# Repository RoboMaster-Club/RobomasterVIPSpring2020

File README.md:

# RobomasterVIPSpring2020

This is the repository for the VIP associated with the Purdue Robomaster team to create a self-guided missile system for the International Robomaster Competition in the Spring 2020 semester. The progress for the project will be documented here and the documentation for each subsystem can be found in their respective folder.

## Overview

The Robomaster 2020 competition added a new robot named the "dart". The dart is a self-guided missile system that will travel across the game field and deal damage to the enemy team's base. The team is also responsible for the creation of a dart launcher that will launch the darts. A more in-depth overview can be found [here](https://docs.google.com/presentation/d/1Q_qpdWloxJJ2q0ATfSRlsLZs0-6WAkRAROG2gjLVUHA/edit?usp=sharing). The dart build specification can be found in the [Robomaster Robot Specification Manual](http://rm-static.djicdn.com/documents/13194/b4177a18f71e31577802511685160062.pdf).

## Team Members

* Kurtis Dressel
* Henry Silva
* Dansen Wang

## Updates

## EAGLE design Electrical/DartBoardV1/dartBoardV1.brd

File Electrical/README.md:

# Dart Electrical Subsystem

## Contributers
* Henry Silva

## Updates

### Week 12 (4/6 - 4/11)

The team has decided to switch to SPI instead of using i2c because of its speed advantages and because there are only 2 slave devices on the dart. I will now go on a long winded account of how I got spi to work on the stm32 with an arduino as slave because if I dont write this down I am going to forget. I tested both full duplex slave and half duplex recieve only with both hardware nss diasbled and enabled all of them worked. I did not figure out how to do an interrupt with the hardware nss but I was able to simulate slave select by creating a gpio input on PC2 that acted as a slave select. The stm32 will only try and listen when PC2 is held low. To recieve the data sent by the arduino use HAL_SPI_Receive. I had issues with the stm32 reading the sent data incorrectly. I was able to fix this with 2 changes. 
1. Inserting a small delay (10 milliseconds) between the arduino pulling the slave select low and sending the data. 
2. Setting the number of bytes to recieve in the HAL_SPI_Receive call by 1 more than the number of bytes that you wish to recieve
3. A relatively small timeout period (50 milliseconds) on the HAL_SPI_Receive call.

This ensures that the stm32 will read the data being sent to it completely and correctly. This will cause the SPI recieve function to timout every time it is called, but with a short timeout period this should not effect the speed too much. The timeout period may have to be increased if the amount of bytes being read is increased by a lot.

### Week 11 (3/29 - 4/5)

Since we have decided to use the stm32 and the raspberry pi, a way to communicate between the two is needed. I2C seems like a good choice because it would allow the raspberry pi to use one protocol to communicate with the accelorometer and the stm32. In the I2C system, the master would be the raspberry pi and the stm32 and any other sensor would be the slave devices. The raspberry pi would first initialize any sensors on board and send any initial data to the stm32. The commands to the stm32 would be sent by the pi and stored in some of the data registers on the stm32.

### Week 9 (3/15 - 3/22)

Given the new situation that we are in, I have decided to prioritize what I think can be realistically done while not on campus and better prepare for a testing prototype to be completed early next fall semester. Currently, I am tasked with creating the magnetic actuators and making a testing interface for the test rig. I am not confident that I can produce the coils needed for the magnetic actuator at home, at least of the quality that would be acceptable for a testing prototype. I already have actuators that I could test the electronics with and could create more if needed, but not for flight test purposes. I could make progress on the research and development of the methods to create the magnetic actuators. The current plan is to either 3D print the coil wrapping base and wrap it with tape or 3d print a mold to make it out of wax.

For the testing interface, the dart would not need to run off of the onboard raspberry pi. An outside control system can be used instead. This gives me the freedom to choose any platform to run the test rig. The requirments of the testing interface would be live, fine control of the control surfaces of the dart and to recieve data from the sensors on the dart such as the accelerometer and gyro. Data from the change in angle of the dart and what the actuators are set to will be neccessart to create the autonomous control system for the dart. I first considered using an arduino, but having a digital interface with keyboard and controller inputs would be difficult to create from scratch. This is also the same problem for using a raspberry pi. Based on my advisors suggestion, I looked into using a myRio. This solution seems attractive because labview can be used to easily create a testing interface that can also display live data. The only problem with this solution is that I do not have a myRio and they are not cheap. I would have easily been able to borrow one from the ME department, but I am no longer on campus.

### Week 7 (3/1 - 3/7)

Following the decision to use the raspberry pi zero for the vision processing, I was tasked with finding a way to control the magnetic actuators and get data from the imu either with the raspberry pi or by interfacing the pi with a microcontroller. After discussing with others with more experience, I decided to use an stm32 along with the pi.Since the pi will be doing vision processing it will be more reliable to send commands for the stm32 to perform rather than having the pi create pwm signals and communicate with the imu. This also means that the stm32 will have to communicate information back to the pi. I was then faced with two decisions, either send IMU data to the pi and have the pi calculate the appropriate actions for the stm32 to perform or have the pi send vision data to the stm32 and have the stm32 determine the appropriate actions for the actuators. I decided on the first option because it keeps the control calculations on the pi, which already has the vision data, and it would be faster to develop code for the pi. 

My first step to implementing the new changes was to update the elecitrcal schematic. I noticed that the current micrcontroller was the stm32f407. The 407 was chosen because of its camera interfacing features, but those are no longer needed in the new design. I decided to switch to the stm32f05, the same microcontroller on the [adafruit feather express](https://www.adafruit.com/product/4382). This will allow to test on a platform that I already have. It is also smaller than the stm32f07 and does not come with features that are not needed. After updating the schematic with the new microcontroller and motor drivers. I also had to connect the pi to the stm32f405 so that they can communicate with each other. I connected the TX and RX pins on the Pi to the RX and TX pins on the stm32f405. I used stm32CubeIDE to assign the pins on the stm32f405 to their functions. From previous experience, when communicating through uart between two devices you have to make sure that they are using the same uart protocol. The two most common are ttl and rs232. After some research, I found out that the pi uses ttl which the stm32 also uses, so no converter would be needed.

The next step was to find connectors to connect the battery and magnetic actuators. Given the size constraints, micro jst connectors with 1mm pitch would be the smallest solution to the problem. The [header](https://www.digikey.com/product-detail/en/jst-sales-america-inc/SM02B-SRSS-TB-LF-SN/455-1802-1-ND/926873), [housing](https://www.digikey.com/product-detail/en/jst-sales-america-inc/SHR-02V-S-B/455-1377-ND/759866), and [contact](https://www.digikey.com/product-detail/en/jst-sales-america-inc/SSH-003T-P0-2-H/455-2963-1-ND/5725854) are all really small and will probably be difficult to crimp, but it is worth it because of the small size of the board. One concern is that the current limit is 1 Amp, so if the whole circuit or any of the actuators needs to draw over an amp another solution will have to be found.

### Week 6 (2/23 - 3/1)

At the start of this week, I ordered the parts for the next magnetic actuator prototype. I bought the [DRV8835 Dual Motor Driver Carrier](https://www.pololu.com/product/2135) from Pololu. For the magnets, I ordered two different sizes, one for the [inner magnet](https://supermagnetman.com/products/cyl0052?_pos=1&_sid=c6e9fa681&_ss=r&variant=11410243843) and [another](https://supermagnetman.com/products/d1001b?_pos=1&_sid=058eb5170&_ss=r&variant=11410255619) for the outside centering magnet. For the inside of the actuator two of the magnets will be placed in between the pivoting rod. Two of the outer magnets will be used to center the inner magnets when the actuator is not powered. They will also be used to provide a counter torque to enable the degree of rotation based on the PWM signal.

After getting the new magnets, a new prototype for the actuator was designed and printed. The new design is smaller and is closer to the size that we will want it to be to go on the dart. After the magnets were placed in the rotating part of the actuator and the wire coiled around the outside, the tests were ready to begin. The code I used to test the actuator can be found [here](https://github.com/RoboMaster-Club/spring-2020-vip-course/blob/master/Electrical/driverTest/driverTest.ino). I conducted test on both the old and new prototype. I first tested moving the actuator from one side to the other. Both the new and old prototype were able to do this quickly and with reasonable force. The second test used magnets on the outside along with changing the pwm signal to control the angle of the actuator. I was able to control the angle, but the movement between angles was not perfectly smooth and the actuator would sometimes get stuck. This is most likely due to the magnets on the outside not being perfectly straight or held in place. There is also no bearing on the inside of the actuator and the coil is not perfectly wrapped. Smoother movement was able to be done by increasing the voltage put through the coil, but it was still not perfect. The new prototype drew 0.8 amps at 2 volts and just over 1 amp at 2.5 volts. It also would get hot when run for longer than 30 seconds at 2.5 volts, but could run for a prolonged period of time without getting hot at 2 volts. These findings raise some concerns for my plans to run the actuators at the battery voltage (3.7 volts). The heat is not an issue because of the short flight time, but the current motor driver has a current limit of 1.2 amps per output channel. More tests will have to be done with the final design of the actuator to determine if a buck converter will be needed to drive the actuator.

Old design side to side

Old design angle control

New design angle control

### Week 5 (2/17 - 2/23)

Since the pcb would need a motor driver in order to provide enough current to use the magnetic actuator, I started my search for an appropriate motor controller. The first one I found was the [L298](https://www.sparkfun.com/datasheets/Robotics/L298_H_Bridge.pdf) full bridge motor driver. It looked like a good choice for a motor controller because it had 4 outputs for the 4 actuators that would be on the dart. It also has a max current output of up to 4A, which is more than enough to run the actuators. I replaced the 4 servo outputs with the new motor driver on the current dart schematic. I then realized that I would need a buck converter to step down the voltage from 3.7V to 3.3V that would run the logic, ATMEGA, and IMU. I used the [LM3671](http://www.ti.com/product/LM3671) that I have used in past projects. I would also need to boost the 3.7V to 5V to power the motor driver and actuators, but after some research into a converter I decided to look for 3.3V motor drivers because it would be inefficient to convert to 5V just for the motor driver and it would make the circuit smaller is everything ran on 3.3V. I found [this website](https://www.pololu.com/category/11/brushed-dc-motor-drivers) with many motor driver breakout boards for smaller motors. The actuators would not need the higher current output of the previous motor driver, so using a lower current one would not be a problem. The motor drivers on the site had only 2 outputs max, so I would need 2 of the drivers to control all the actuators. I decided on the [DRV8835](https://www.digikey.com/product-detail/en/texas-instruments/DRV8835DSSR/296-30391-1-ND/3188673) because it is small and can output a max current of 1.5A and runs off of 3.3V logic.

Using the guide that I found last week to make a magnetic actuator, I attempted to make one using some neodinium magnets and magnet wire I bought. I used a L298 breakout board as the motor driver. I first make a coil by wrapping around a pencil and turned the wire about 100 times. After hooking up the coil to the motor driver controlled by an arduino nano, I was not able to get a reaction from the magnet. I decided that I did not wrap the coil around enough and made another coil with about 500 turns. The coil was big compared to the magnet, but I was able to vibrate the magnet when I brought it close to the coil. I considered the test a minor success given that I was able to get a reaction out of the magnet.

After the team meeting on friday, another team member and I wanted to try to make a working prototype actuator based on the design from the guide. We 3D printed the actuator which was made up of a cylinder with another piece with pegs that held the magnet within it. The coil was wrapped around the cylinder using a drill to make a tight coil. We tested the actuator by hooking it directly up to a power supply with 1 volt output. At 1 volt, the actuator drew half an amp. The state of the actuator could be controlled by switching the polarity. The actuator was able to switch quickly and with reasonable force.

Goals For Next Week:
* Make another actuator prototype with new design, smaller magnets, and new motor driver
* Keep schematic updated and make changes as needed

### Week 4 (2/9 - 2/16)

I was tasked with getting the position of the dart from the launch point by using data from the accelerometer. After a bit of research, I decided that it would not be a good idea. I explain more about it at the end of my update report from last week. Since I abandoned that objective, I decided that making more progress on the custom pcb would be a good idea. My current schematic uses the stm32f4 as the microcontroller, but I am not confident in making that decision for the rest of the team. I decided to make another schematic using the atmega328p as the micro. I also decided to make a table of all the components on the dart and their power consumption. To find the voltages and draw, I looked at the datasheets for the atmega, pixy2, and the IMU. I was not able to find a data sheet for the servos, but after some research I concluded that the servos would draw about 200 mA between all of them since they would not be under high load. I did not know the power draw of the dart trigger device, but my guess is that it is minimal. Since the dart will only have to be on for less than 30 minutes and only flying for 5 seconds, a small battery will work just fine. A capacitor would require a constant power connection to the dart launcher and would also require an outside contact on the dart.

|Device|Voltage (V)|Power Draw (mA)|Watts|
|----------|------|----------|------|
|atmega328p|	3.3	|1.5|	0.00495|
|pixy2|	5	|140|	0.7|
|lsm6ds3|	3.3	|1	|0.0033|
|Servo (3)|	5|200|	1|
|DTD|	?	|?	|?|

After the team meeting on friday, I got a clearer message of what we want to use onthe dart. It was decided that the atmega328p would be the microcontroller on the dart. The body of the dart was also changed from a lifting body to a more missile shaped projectile. This would change the dimensions of the electronics board, but it will still have enough space to fit everything. Based on the suggestions of one of the faculty advisors, we are going to try and switch from servos to a magnetic actuator. A magnetic actuator is a magnet placed in a coil of wire. Driving current through the wire will cause a magnetic field that will force the magnet to rotate in the direction of the magnetic field. The field can be reversed by switching the polarity of the coil. After doing some searching online, I could not find a vendor for magnetic actuators that would arrive in a reasonable amount of time. I did, however, find multiple [tutorials](https://hackaday.com/2018/04/17/diy-magnetic-actuator-illustrated-and-demonstrated/) on how to make them.

Goals for Next Week:
* Make DIY magnetic actuator and test it
* Start pcb design based on new dart body using atmega and magnetic actuators

### Week 3 (2/2 - 2/9)

My task this week is to research and implement code that will take measurements from an IMU and control servos in order to simulate the dart's response. I first had to figure out how to get data from the IMU I was given. The IMU is the [MPU-9250](https://www.invensense.com/products/motion-tracking/9-axis/mpu-9250/) breakout board. The microcontroller is the arduino nano and the two servos are SG90 micro servos. I first tried to look for stabilization code used for an arduino nano controlled gimbal with servos, but my search came dry with only a few examples that used the IMU I had and none of them were very well documented. I decided to look for example code for the IMU just to get some data out from it and put on the serial monitor. I found sparkfun's example code and library [here](https://github.com/sparkfun/SparkFun_MPU-9250_Breakout_Arduino_Library/blob/master/examples/MPU9250BasicAHRS_I2C/MPU9250BasicAHRS_I2C.ino). I uploaded the example code and after changing the address of the IMU in the code that I found using an [I2C scanner](https://playground.arduino.cc/Main/I2cScanner/), I saw a lot of data output to the console.

The example has a lot of code that I do not need, such as code to display the information to an LCD screen. The program also has options for more advanced output that I also removed. I only wanted the yaw, pitch, and roll values for servo adjustment. I know had to figure out how to control the servos to adjust the pitch and roll. I know that I could just use if statements, but using PID would be better. PID is used to control a system more precisely than just using if statements. I did not know how to use PID with arduino, so I did some searching on Youtube to find an example. This [video](https://www.youtube.com/watch?v=crw0Hcc67RY) does a good job of explaning how to use PID to conrtol an LED with data from a sensor. I now had to apply this to the servos and IMU data. The PID library can be found on [github](https://github.com/br3ttb/Arduino-PID-Library), but can also be added to the arduino IDE through the library manager. I follwed the example from the video and applied it to the IMU yaw data and one of the servos.

After setting up the other two servos, I had to do some PID tuning to get the appropriate response that I wanted. The current input from the IMU gives yaw, pitch, and roll from -90 to 90 degrees. This range of values has to be turned into a range from 0 to 90 or 0 to 180 degrees since the PID library I am using does not work with values above the target value (for example when the target value is 0, the PID computation will output zero for any measurement above zero, so it will only work with negative values). My first attempt to transfer the values was to use the absolute value of the angle and move the servo to the right or left depending on if it was negative or positive. This does not work very well because the PID computation does not know the difference between the positive and negative values. If the yaw were to change from -10 to 10 degrees, the PID loop would think that the value did not change and increase its output. I decided to wait and get some help about how to approach this problem as I did not think I was going in the right direction.

After Friday's team meeting, it was explained to me that control and where the dart is in space are two different problems. I was tasked with first finding the information for where the dart is and then trying to find out how to get it where it needs to be. I know that position can be solved for from acceleration data by taking the double integral, but I did some research to see how possible it was given our hardware. From past experience, I know that getting position information from acceleration data results in a lot of error, my research also supports my previous experience. [This](http://www.chrobotics.com/library/accel-position-velocity) page from a website that sells orientation sensors states that getting position from acceleration data is not accurate enough to be useful with their hardware (their sensors sell for upwards of 200 dollars) and that hardware that is significantly more expensive would be needed in order to get accurate data. I decided that it would be a waste of time to look for solutions for this problem.

### Week 2 (1/26 - 2/2)

This week I was tasked with creating a schematic for the electrical system that we have been decided on thus far. I decided that the stm32f4 I found from my research last week would be used in the schematic. I first consulted the [stm32f4 datasheet](https://www.st.com/content/ccc/resource/technical/document/reference_manual/3d/6d/5a/66/b4/99/40/d4/DM00031020.pdf/files/DM00031020.pdf/jcr:content/translations/en.DM00031020.pdf) to see how it is powered. I could not find what I was looking for, but after some more research I found the [stm32f4 application note](https://www.st.com/content/ccc/resource/technical/document/application_note/76/f9/c8/10/8a/33/4b/f0/DM00115714.pdf/files/DM00115714.pdf/jcr:content/translations/en.DM00115714.pdf) which includes a sample schematic and an in depth description on the hardware needed for power (such as decoupling capacitors) and other functions. 

After placing the appropriate power hardware in the schematic, I then had to search for how to connect the [OV7670](https://www.arducam.com/wp-content/uploads/2019/11/Arducam_ov7670_cmos_camera_module_revc_ds.pdf) camera to the stm32f4. I found a github [repository](https://github.com/iwatake2222/DigitalCamera_STM32) that included the port assignment of the stm32f4 which helped me figure out which pins to connect the camera to. Since the camera uses I2C, pullup resistors were required on the schematic. I used the STM32CubeMX software to keep track of the pin functions and find pins that I could use for PWM and the IMU. I found that PWM just uses a pin with GPIO output that is turned on and off based on a timer, so I assigned two pins for the two servos.

The next part was to find a suitable IMU for acceleration and gyro measurements. I first went to adafruit and sparkfun to find what breakout boards they had for IMUs. I wanted to find an IMU that only had the measurements that I needed and nothing else to keep it simple and cheap. I found the [LSM6DS3](https://www.st.com/content/ccc/resource/technical/document/datasheet/group0/2e/84/27/34/60/8d/49/f2/DM00237513/files/DM00237513.pdf/jcr:content/translations/en.DM00237513.pdf) which provides 3D digital accelerometer and a 3D digital gyroscope. Using sparkfun's eagle files found on their [product page](https://www.sparkfun.com/products/13339), I was able to add the sensor to my schemtic with the appropirate components to power it.

I decided that I would use small jst connectors ([like this one](https://www.digikey.com/product-detail/en/jst-sales-america-inc/SM03B-GHS-TB(LF)(SN)/455-1565-1-ND/807833)) to connect the servos and battery. I then searched for a battery to power the dart while in flight. Since the stm32 and the IMU run off of 3.3v, a battery around that voltage would be preferred, but not manditory since the voltage could be regulated. I saw several 3.7V lithium ion batteries that were under the 4Wh limit set by the competition rules. Since the time of flight will be short (around 5 seconds) I decided that a small battery would be better for the weight limit. I found a selection of lithium ion batteries in the 300 to 500 mAh output range that were under 20 grams such as this [one](https://www.digikey.com/product-detail/en/sparkfun-electronics/PRT-13851/1568-1493-ND/6605199).

Schematic

STM32 Pinout

#### Goals For Next Week

Since the team's meeting about what was done this week and what we are going to prioritize, I have been moved from creating a custom PCB for the time being until we decide on what we want hardware wise on the dart. We also want to focus on getting a prototype out as fast as possible. I am tasked with using an arduino nano with an IMU to drive servos based on the measurements of the imu.

My tasks are as follows:

* Research and find stabilization code that uses input from an IMU in order to keep a plane (or other flying object) level
* Get the IMU and servos working on the arduino nano
* Have a working prototype that could could be put into a prototype dart body and, with some tweaking, be able to be tested

### Week 1 (1/19 - 1/26)

I was tasked with researching the microcontroller and any other electrical components that might be used to control the dart or dart launcher. In the previous meeting, it was decided that the stm32 would be the best choice for the microcontroller. 
Since a camera will be needed for vision targeting, I searched for a stm32 cameras. This lead me to the [DCMI](https://www.st.com/content/ccc/resource/technical/document/application_note/group0/c0/ef/15/38/d1/d6/49/88/DM00373474/files/DM00373474.pdf/jcr:content/translations/en.DM00373474.pdf) (Digital Camera Interface) for stm32. The DCMI allows for the easy connection of a camera to the stm32. The document also lists stm32 models that have DCMI included.

This narrowed down the search for which stm32 to decide on. I looked on digikey for the compatible stm32s and settled on the stm32f4 series because they had the most options and were the cheapest. I decided on the [STM32F407VET6](https://www.digikey.com/product-detail/en/stmicroelectronics/STM32F407VET6/497-12075-ND/2793093) because it seemed to have everything that was required so far for the cheapest price.

In terms of camera modules, the [OV7670](https://www.arducam.com/wp-content/uploads/2019/11/Arducam_ov7670_cmos_camera_module_revc_ds.pdf) seemed to be the most popular one used with the stm32. All image processing functions are fully customizable to customize the camera to what is needed. The resolution of the camera is 640x480, I do not know if that is a good enough resolution given the distance from the target, but if the target gives off enough light it should not be a problem. Although I have found multiple projects that use the camera, I have not found good recent documentation about how to use the camera ([good one but from 2012](https://www.element14.com/community/groups/development-tools/blog/2012/06/11/connecting-an-ov7670-camera-to-the-stm32f4-discovery-board)). More research will be needed if we go along with this choice.

I also did some research into rtos (Real time operating system). From what I understand, it will help the scheduling of tasks so that there is a predictable execution pattern. This also ensures that real time requirements are met (such as a change in the postition of the target relative to the dart, that change being detected, and an appropriate control response that happens in a certain amount of time). I am not sure if a rtos is necessary since the amount of processes running at once will probably not be high, but it also allows programs to pass information to each other and be modular. The information I stated above and more can be found [here](https://www.freertos.org/about-RTOS.html).

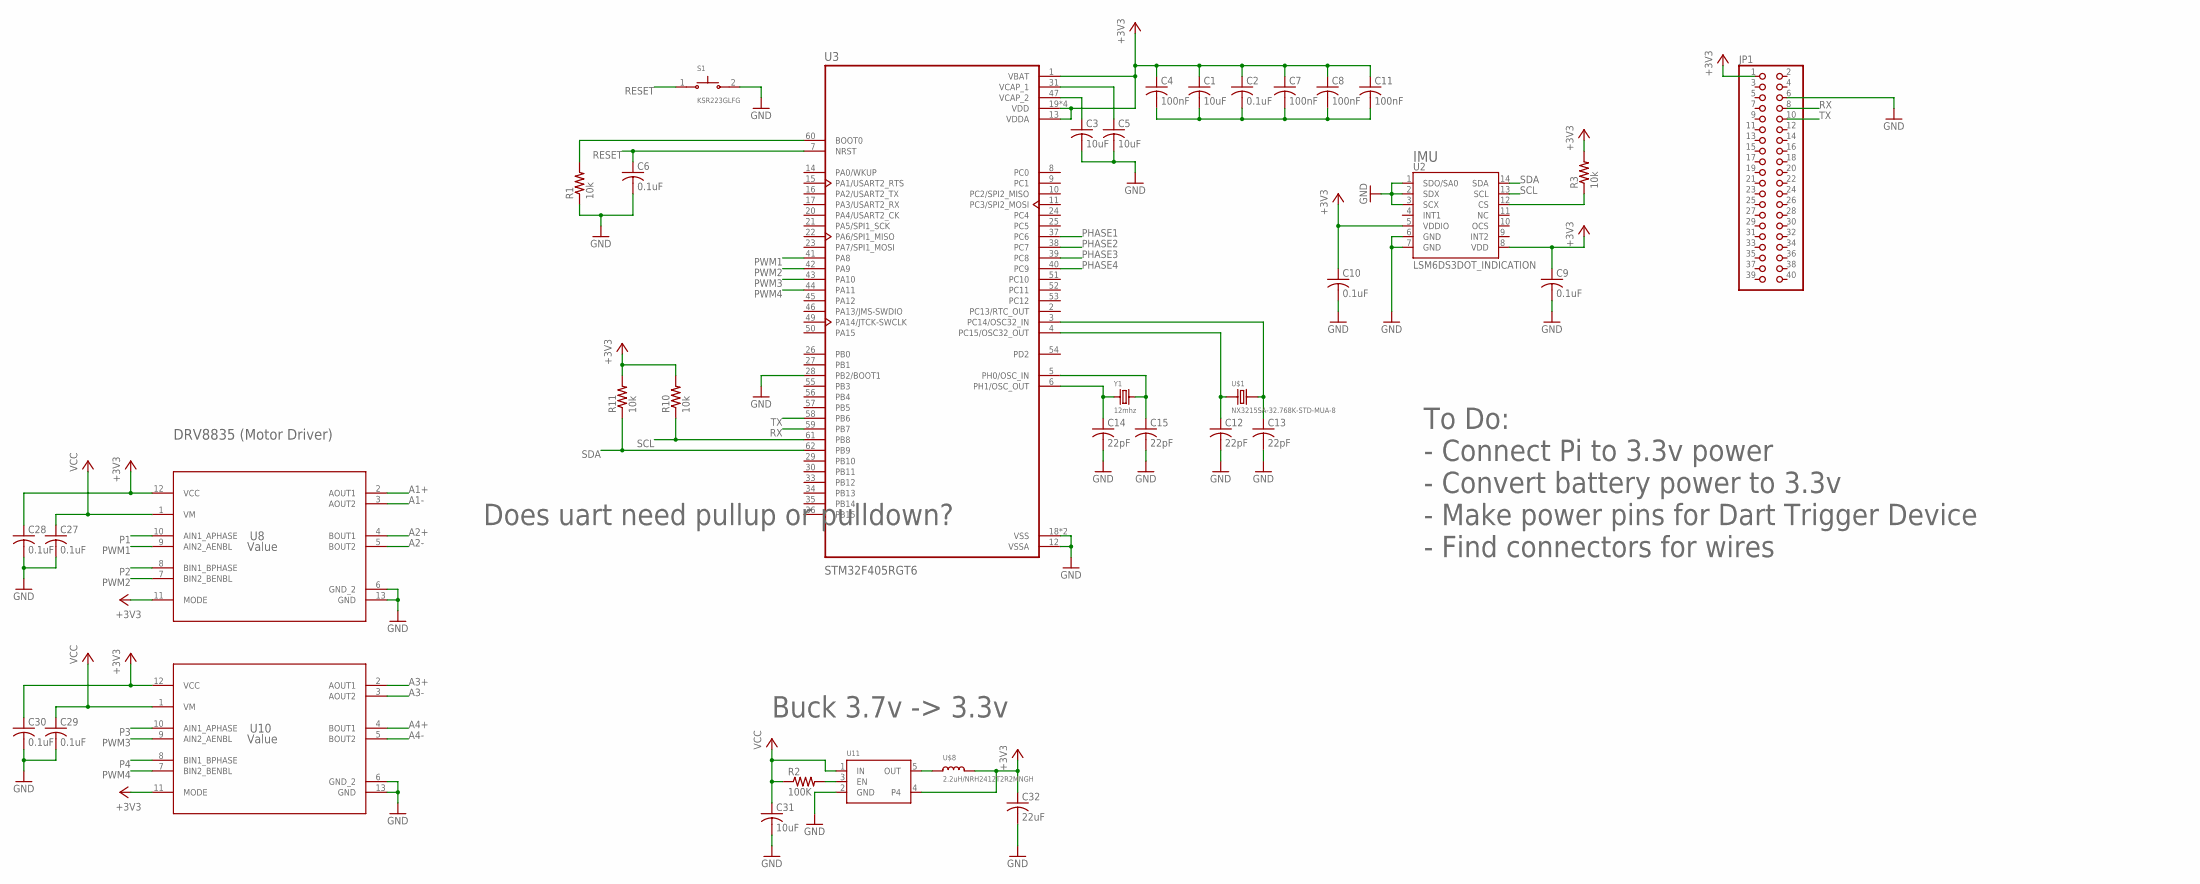
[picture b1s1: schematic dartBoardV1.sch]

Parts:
C1, C3, C5, C31: 10uF; C0603
C2, C6, C9, C10, C27, C28, C29, C30: 0.1uF; C0603
C4, C7, C8, C11: 100nF; C0603
C12, C13, C14, C15: 22pF; C0603
C32: 22uF; C0603
JP1: PINHD-2X20; 2X20
R1, R3, R10, R11: 10k; R0603
R2: 100K; R0603
S1: KSR223GLFG; SW_KSR223GLFG
U2: LSM6DS3DOT_INDICATION; LGA14L_DOT_INDICATOR
U3: STM32F405RGT6; QFP50P1200X1200X160-64N
U8, U10: Value; DSS0012A
U11: VREG_SOT23-5; SOT23-5
U$1: NX3215SA-32.768K-STD-MUA-8
U$8: 2.2uH/NRH2412T2R2MNGH; MDKK1616T2R2MM
Y1: 12mhz; CRYSTAL_2.5X2

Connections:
+3V3: C1.1, C2.1, C4.1, C7.1, C8.1, C9.1, C10.1, C11.1, C28.1, C30.1, C32.1, JP1.1, R3.2, R10.2, R11.2, U2.5 (VDDIO), U2.8 (VDD), U3.1 (VBAT), U3.13 (VDDA), U3.19 (VDD), U3.32 (VDD), U3.48 (VDD), U3.64 (VDD), U8.11 (MODE), U8.12 (VCC), U10.11 (MODE), U10.12 (VCC), U11.4, U$8.P$2 (2)
A1+: U8.2 (AOUT1)
A1-: U8.3 (AOUT2)
A2+: U8.4 (BOUT1)
A2-: U8.5 (BOUT2)
A3+: U10.2 (AOUT1)
A3-: U10.3 (AOUT2)
A4+: U10.4 (BOUT1)
A4-: U10.5 (BOUT2)
GND: C3.2, C5.2, C6.2, C9.2, C10.2, C12.2, C13.2, C14.2, C15.2, C27.2, C28.2, C29.2, C30.2, C31.2, C32.2, JP1.6, R1.1, S1.2, U2.1 (SDO/SA0), U2.2 (SDX), U2.3 (SCX), U2.6 (GND), U2.7 (GND), U3.12 (VSSA), U3.18 (VSS), U3.28 (PB2/BOOT1), U3.63 (VSS), U8.6 (GND_2), U8.13 (GND), U10.6 (GND_2), U10.13 (GND), U11.2 (GND)
unnamed: R3.1, U2.12 (CS)
unnamed: C12.1, U3.4 (PC15/OSC32_OUT), U$1.P$1 (1)
unnamed: C1.2, C2.2, C4.2, C7.2, C8.2, C11.2
unnamed: C13.1, U3.3 (PC14/OSC32_IN), U$1.P$2 (2)
unnamed: C5.1, U3.31 (VCAP_1)
unnamed: C3.1, U3.47 (VCAP_2)
unnamed: R1.2, U3.60 (BOOT0)
unnamed: C14.1, U3.6 (PH1/OSC_OUT), Y1.1
unnamed: C15.1, U3.5 (PH0/OSC_IN), Y1.3 (2)
unnamed: R2.2, U11.3 (EN)
unnamed: U11.5 (OUT), U$8.P$1 (1)
P1: U8.10 (AIN1_APHASE)
P2: U8.8 (BIN1_BPHASE)
P3: U10.10 (AIN1_APHASE)
P4: U10.8 (BIN1_BPHASE)
PHASE1: U3.37 (PC6)
PHASE2: U3.38 (PC7)
PHASE3: U3.39 (PC8)
PHASE4: U3.40 (PC9)
PWM1: U3.41 (PA8), U8.9 (AIN2_AENBL)
PWM2: U3.42 (PA9), U8.7 (BIN2_BENBL)
PWM3: U3.43 (PA10), U10.9 (AIN2_AENBL)
PWM4: U3.44 (PA11), U10.7 (BIN2_BENBL)
RESET: C6.1, S1.1, U3.7 (NRST)
RX: JP1.8, U3.59 (PB7)
SCL: R10.1, U2.13 (SCL), U3.61 (PB8)
SDA: R11.1, U2.14 (SDA), U3.62 (PB9)
TX: JP1.10, U3.58 (PB6)
VCC: C27.1, C29.1, C31.1, R2.1, U8.1 (VM), U10.1 (VM), U11.1 (IN)

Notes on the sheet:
IMU
To Do: - Connect Pi to 3.3v power - Convert battery power to 3.3v - Make power pins for Dart Trigger Device - Find connectors for wires
DRV8835 (Motor Driver)
Buck 3.7v -> 3.3v
Does uart need pullup or pulldown?

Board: 2 copper layers, 36 parts (0 on the bottom side), 23 nets, no tracks yet.

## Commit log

2020-01-23 fixed file
2020-01-24 added outline for arduino dart aiming algorithm
2020-01-24 Update README.md Week 1
2020-01-25 Create JeffDocument
    1/24 modified
2020-01-31 Add files via upload
    Pictures supporting week one's push
2020-01-31 README.MD
    Week one's work was updated and pushed, working on week two
2020-01-31 Create Mark1 CAD screenshot
2020-01-31 Update README.md Week 2
2020-02-09 added images folder
2020-02-09 3rd Progress Report
2020-02-10 Add files via upload
    The three components of the target dummy main body
2020-02-10 Update README.md
    updated for week three
2020-02-24 Added opencv testing scripts
2020-02-24 Added images
2020-02-24 Added 4th and 5th progress reports
2020-02-25 added board and schematics
2020-02-25 deleted test files
2020-02-25 motor driver test code
2020-02-28 updated driver tests
2020-03-05 New schematic
2020-03-09 Added two different ways to detect circles
2020-03-23 added light detection scripts
2020-03-23 added progress reports
2020-03-23 small fix
2020-03-30 added dart control code and modified existing algorithms
2020-03-30 Added Week 10 Progress Report
2020-04-06 Added C++ object detection and control code
2020-04-06 Added Progress Report
2020-04-06 minor fix
2020-04-10 added SPI communication code
2020-04-10 added spi test
2020-04-17 converted spiTest.py to spiTest.cpp
2020-04-19 organized code and added first half flgith dart control
2020-04-20 fixed compile errors
2020-04-22 added sensor test code
2020-05-14 added raspberry pi bno055Test

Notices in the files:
parts and their libraries:
microbuilder: This work is placed in the public domain, and may be freely used for commercial and non-commercial work with the following conditions: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
